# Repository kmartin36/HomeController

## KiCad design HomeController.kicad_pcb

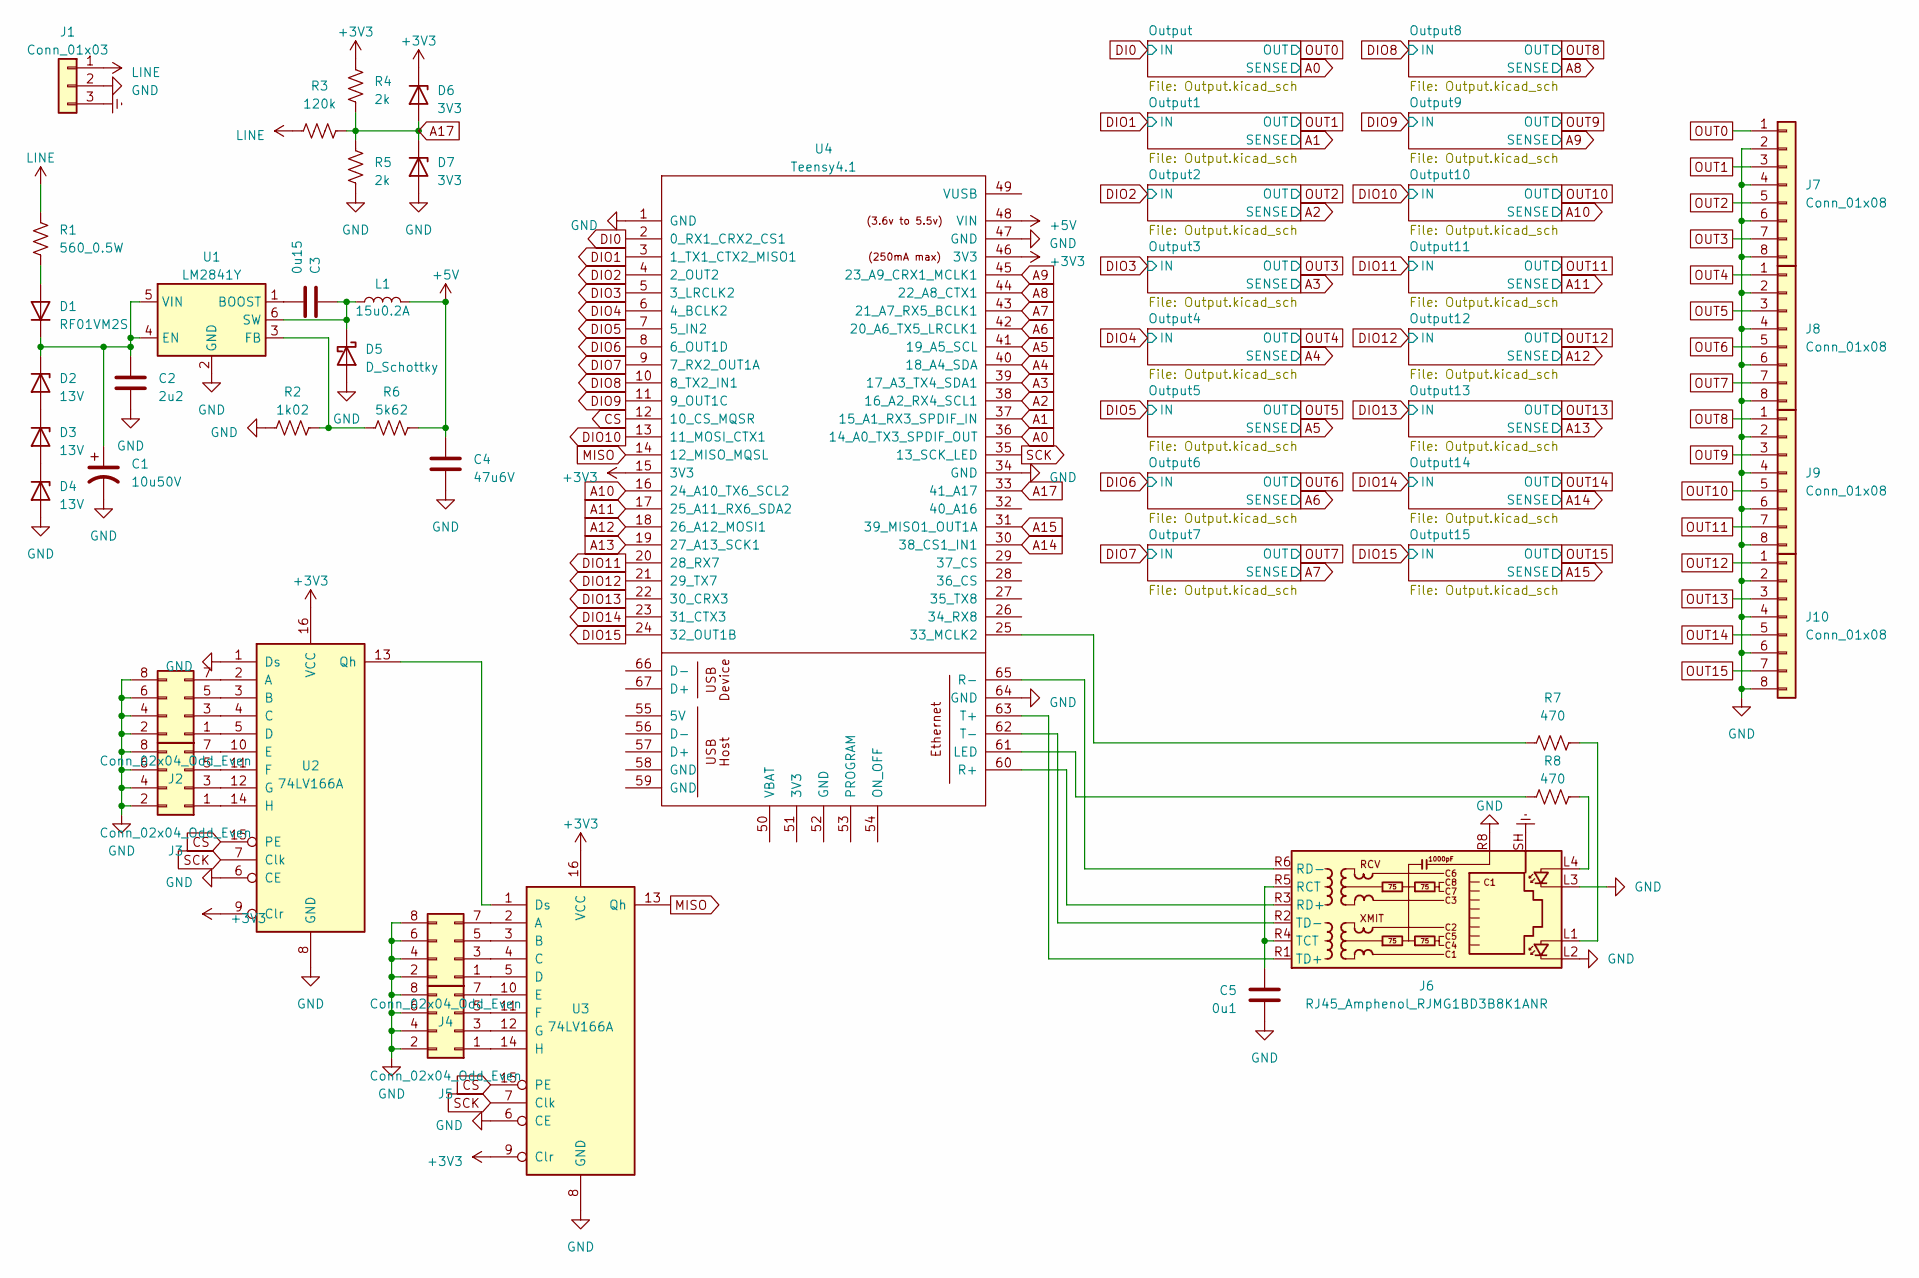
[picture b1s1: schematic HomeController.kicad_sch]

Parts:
C1: 10u50V; L_0805_2012Metric_Pad1.15x1.40mm_HandSolder
C2: 2u2; C_0603_1608Metric_Pad1.08x0.95mm_HandSolder
C3: 0u15; C_0603_1608Metric_Pad1.08x0.95mm_HandSolder
C4: 47u6V; C_0805_2012Metric_Pad1.18x1.45mm_HandSolder
C5: 0u1; C_0603_1608Metric_Pad1.08x0.95mm_HandSolder
D1: RF01VM2S; D_SOD-323
D2, D3, D4: 13V; D_SMA-SMB_Universal_Handsoldering
D5: D_Schottky; D_SC-80_HandSoldering
D6, D7: 3V3; D_SOD-323_HandSoldering
J1: Conn_01x03; PhoenixContact_MCV_1,5_3-G-5.08_1x03_P5.08mm_Vertical
J2, J3, J4, J5: Conn_02x04_Odd_Even; PhoenixContact_MCV_1,5_8-G-5.08_1x08_P5.08mm_Vertical
J6: RJ45_Amphenol_RJMG1BD3B8K1ANR
J7, J8, J9, J10: Conn_01x08; PhoenixContact_MCV_1,5_8-G-5.08_1x08_P5.08mm_Vertical
L1: 15u0.2A; L_0805_2012Metric_Pad1.15x1.40mm_HandSolder
R1: 560_0.5W; R_1210_3225Metric_Pad1.30x2.65mm_HandSolder
R2: 1k02; R_0603_1608Metric_Pad0.98x0.95mm_HandSolder
R3: 120k; R_1206_3216Metric_Pad1.30x1.75mm_HandSolder
R4, R5: 2k; R_0603_1608Metric_Pad0.98x0.95mm_HandSolder
R6: 5k62; R_0603_1608Metric_Pad0.98x0.95mm_HandSolder
R7, R8: 470; R_0603_1608Metric_Pad0.98x0.95mm_HandSolder
U1: LM2841Y; TSOT-23-6
U2, U3: 74LV166A; TSSOP-16_4.4x5mm_P0.65mm
U4: Teensy4.1; Teensy41

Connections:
+3V3: D6.1 (K), R4.1, U2.9 (Clr), U2.16 (VCC), U3.9 (Clr), U3.16 (VCC), U4.15 (3V3), U4.46 (3V3); also elsewhere on the board
+5V: C4.1, L1.2, R6.1, U4.48 (VIN)
A0: U4.36 (14_A0_TX3_SPDIF_OUT); also elsewhere on the board
A1: U4.37 (15_A1_RX3_SPDIF_IN); also elsewhere on the board
A2: U4.38 (16_A2_RX4_SCL1); also elsewhere on the board
A3: U4.39 (17_A3_TX4_SDA1); also elsewhere on the board
A4: U4.40 (18_A4_SDA); also elsewhere on the board
A5: U4.41 (19_A5_SCL); also elsewhere on the board
A6: U4.42 (20_A6_TX5_LRCLK1); also elsewhere on the board
A7: U4.43 (21_A7_RX5_BCLK1); also elsewhere on the board
A8: U4.44 (22_A8_CTX1); also elsewhere on the board
A9: U4.45 (23_A9_CRX1_MCLK1); also elsewhere on the board
A10: U4.16 (24_A10_TX6_SCL2); also elsewhere on the board
A11: U4.17 (25_A11_RX6_SDA2); also elsewhere on the board
A12: U4.18 (26_A12_MOSI1); also elsewhere on the board
A13: U4.19 (27_A13_SCK1); also elsewhere on the board
A14: U4.30 (38_CS1_IN1); also elsewhere on the board
A15: U4.31 (39_MISO1_OUT1A); also elsewhere on the board
A17: D6.2 (A), D7.1 (K), R3.2, R4.2, R5.1, U4.33 (41_A17)
CS: U2.15 (PE), U3.15 (PE), U4.12 (10_CS_MQSR)
DI0: U4.2 (0_RX1_CRX2_CS1); also elsewhere on the board
DIO1: U4.3 (1_TX1_CTX2_MISO1); also elsewhere on the board
DIO2: U4.4 (2_OUT2); also elsewhere on the board
DIO3: U4.5 (3_LRCLK2); also elsewhere on the board
DIO4: U4.6 (4_BCLK2); also elsewhere on the board
DIO5: U4.7 (5_IN2); also elsewhere on the board
DIO6: U4.8 (6_OUT1D); also elsewhere on the board
DIO7: U4.9 (7_RX2_OUT1A); also elsewhere on the board
DIO8: U4.10 (8_TX2_IN1); also elsewhere on the board
DIO9: U4.11 (9_OUT1C); also elsewhere on the board
DIO10: U4.13 (11_MOSI_CTX1); also elsewhere on the board
DIO11: U4.20 (28_RX7); also elsewhere on the board
DIO12: U4.21 (29_TX7); also elsewhere on the board
DIO13: U4.22 (30_CRX3); also elsewhere on the board
DIO14: U4.23 (31_CTX3); also elsewhere on the board
DIO15: U4.24 (32_OUT1B); also elsewhere on the board
Earth: J1.3, J6.SH
GND: C1.2, C2.2, C4.2, C5.2, D4.2 (A), D5.2 (A), D7.2 (A), J1.2, J2.2, J2.4, J2.6, J2.8, J3.2, J3.4, J3.6, J3.8, J4.2, J4.4, J4.6, J4.8, J5.2, J5.4, J5.6, J5.8, J6.L2, J6.L3, J6.R8, J7.2, J7.4, J7.6, J7.8, J8.2, J8.4, J8.6, J8.8, J9.2, J9.4, J9.6, J9.8, J10.2, J10.4, J10.6, J10.8, R2.1, R5.2, U1.2 (GND), U2.1 (Ds), U2.6 (CE), U2.8 (GND), U3.6 (CE), U3.8 (GND), U4.1 (GND), U4.34 (GND), U4.47 (GND), U4.64 (GND); also elsewhere on the board
LINE: J1.1, R1.2, R3.1; also elsewhere on the board
MISO: U3.13 (Qh), U4.14 (12_MISO_MQSL)
unnamed: D1.2 (A), R1.1
unnamed: C1.1, C2.1, D1.1 (K), D2.1 (K), U1.4 (EN), U1.5 (VIN)
unnamed: D2.2 (A), D3.1 (K)
unnamed: D3.2 (A), D4.1 (K)
unnamed: C3.1, D5.1 (K), L1.1, U1.6 (SW)
unnamed: J2.1, U2.5 (D)
unnamed: J2.3, U2.4 (C)
unnamed: J2.5, U2.3 (B)
unnamed: J2.7, U2.2 (A)
unnamed: J3.1, U2.14 (H)
unnamed: J3.3, U2.12 (G)
unnamed: J3.5, U2.11 (F)
unnamed: J3.7, U2.10 (E)
unnamed: J4.1, U3.5 (D)
unnamed: J4.3, U3.4 (C)
unnamed: J4.5, U3.3 (B)
unnamed: J4.7, U3.2 (A)
unnamed: J5.1, U3.14 (H)
unnamed: J5.3, U3.12 (G)
unnamed: J5.5, U3.11 (F)
unnamed: J5.7, U3.10 (E)
unnamed: J6.L1, R7.2
unnamed: J6.L4, R8.2
unnamed: C5.1, J6.R4 (TCT), J6.R5 (RCT)
unnamed: J6.R3 (RD+), U4.60 (R+)
unnamed: J6.R6 (RD-), U4.65 (R-)
unnamed: J6.R1 (TD+), U4.63 (T+)
unnamed: J6.R2 (TD-), U4.62 (T-)
unnamed: C3.2, U1.1 (BOOST)
unnamed: R2.2, R6.2, U1.3 (FB)
unnamed: U2.13 (Qh), U3.1 (Ds)
unnamed: R7.1, U4.25 (33_MCLK2)
unnamed: R8.1, U4.61 (LED)
OUT0: J7.1; also elsewhere on the board
OUT1: J7.3; also elsewhere on the board
OUT2: J7.5; also elsewhere on the board
OUT3: J7.7; also elsewhere on the board
OUT4: J8.1; also elsewhere on the board
OUT5: J8.3; also elsewhere on the board
OUT6: J8.5; also elsewhere on the board
OUT7: J8.7; also elsewhere on the board
OUT8: J9.1; also elsewhere on the board
OUT9: J9.3; also elsewhere on the board
OUT10: J9.5; also elsewhere on the board
OUT11: J9.7; also elsewhere on the board
OUT12: J10.1; also elsewhere on the board
OUT13: J10.3; also elsewhere on the board
OUT14: J10.5; also elsewhere on the board
OUT15: J10.7; also elsewhere on the board
SCK: U2.7 (Clk), U3.7 (Clk), U4.35 (13_SCK_LED)

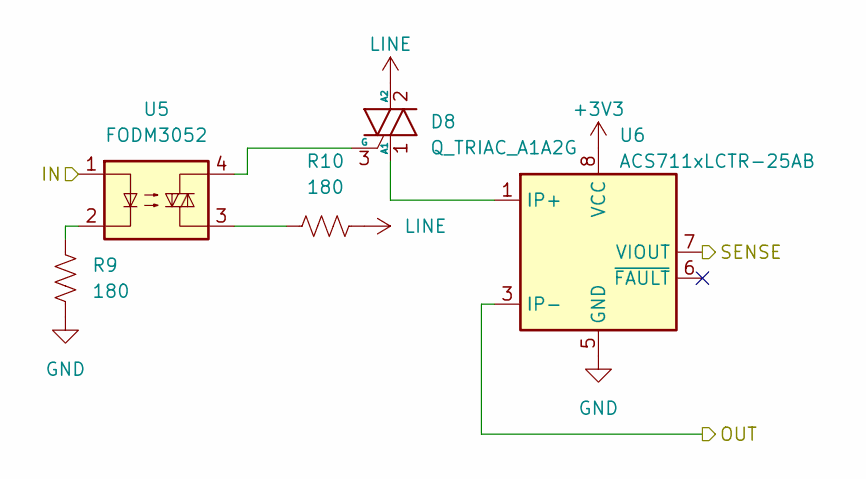
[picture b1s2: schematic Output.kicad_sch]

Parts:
D8: Q_TRIAC_A1A2G; TO-252-2
R9, R10: 180; R_0603_1608Metric_Pad0.98x0.95mm_HandSolder
U5: FODM3052; SMDIP-4_W7.62mm
U6: ACS711xLCTR-25AB; SOIC-8_3.9x4.9mm_P1.27mm

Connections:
+3V3: U6.8 (VCC); also elsewhere on the board
A0: U6.7 (VIOUT); also elsewhere on the board
DI0: U5.1; also elsewhere on the board
GND: R9.2, U6.5 (GND); also elsewhere on the board
LINE: D8.2 (A2), R10.2; also elsewhere on the board
unnamed: D8.1 (A1), U6.1 (IP+), U6.2 (IP+)
unnamed: D8.3 (G), U5.4
unnamed: R9.1, U5.2
unnamed: R10.1, U5.3
OUT0: U6.3 (IP-), U6.4 (IP-); also elsewhere on the board

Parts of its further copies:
D9, D10, D11, D12, D13, D14, D15, D16, D17, D18, D19, D20, D21, D22, D23: Q_TRIAC_A1A2G; TO-252-2
R11, R12, R13, R14, R15, R16, R17, R18, R19, R20, R21, R22, R23, R24, R25, R26, R27, R28, R29, R30, R31, R32, R33, R34, R35, R36, R37, R38, R39, R40: 180; R_0603_1608Metric_Pad0.98x0.95mm_HandSolder
U7, U9, U11, U13, U15, U17, U19, U21, U23, U25, U27, U29, U31, U33, U35: FODM3052; SMDIP-4_W7.62mm
U8, U10, U12, U14, U16, U18, U20, U22, U24, U26, U28, U30, U32, U34, U36: ACS711xLCTR-25AB; SOIC-8_3.9x4.9mm_P1.27mm

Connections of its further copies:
+3V3: U8.8 (VCC), U10.8 (VCC), U12.8 (VCC), U14.8 (VCC), U16.8 (VCC), U18.8 (VCC), U20.8 (VCC), U22.8 (VCC), U24.8 (VCC), U26.8 (VCC), U28.8 (VCC), U30.8 (VCC), U32.8 (VCC), U34.8 (VCC), U36.8 (VCC); also elsewhere on the board
A1: U36.7 (VIOUT); also elsewhere on the board
A2: U10.7 (VIOUT); also elsewhere on the board
A3: U8.7 (VIOUT); also elsewhere on the board
A4: U14.7 (VIOUT); also elsewhere on the board
A5: U12.7 (VIOUT); also elsewhere on the board
A6: U18.7 (VIOUT); also elsewhere on the board
A7: U16.7 (VIOUT); also elsewhere on the board
A8: U22.7 (VIOUT); also elsewhere on the board
A9: U20.7 (VIOUT); also elsewhere on the board
A10: U32.7 (VIOUT); also elsewhere on the board
A11: U24.7 (VIOUT); also elsewhere on the board
A12: U34.7 (VIOUT); also elsewhere on the board
A13: U26.7 (VIOUT); also elsewhere on the board
A14: U28.7 (VIOUT); also elsewhere on the board
A15: U30.7 (VIOUT); also elsewhere on the board
DIO1: U35.1; also elsewhere on the board
DIO2: U9.1; also elsewhere on the board
DIO3: U7.1; also elsewhere on the board
DIO4: U13.1; also elsewhere on the board
DIO5: U11.1; also elsewhere on the board
DIO6: U17.1; also elsewhere on the board
DIO7: U15.1; also elsewhere on the board
DIO8: U21.1; also elsewhere on the board
DIO9: U19.1; also elsewhere on the board
DIO10: U31.1; also elsewhere on the board
DIO11: U23.1; also elsewhere on the board
DIO12: U33.1; also elsewhere on the board
DIO13: U25.1; also elsewhere on the board
DIO14: U27.1; also elsewhere on the board
DIO15: U29.1; also elsewhere on the board
GND: R11.2, R13.2, R15.2, R17.2, R19.2, R21.2, R23.2, R25.2, R27.2, R29.2, R31.2, R33.2, R35.2, R37.2, R39.2, U8.5 (GND), U10.5 (GND), U12.5 (GND), U14.5 (GND), U16.5 (GND), U18.5 (GND), U20.5 (GND), U22.5 (GND), U24.5 (GND), U26.5 (GND), U28.5 (GND), U30.5 (GND), U32.5 (GND), U34.5 (GND), U36.5 (GND); also elsewhere on the board
LINE: D9.2 (A2), D10.2 (A2), D11.2 (A2), D12.2 (A2), D13.2 (A2), D14.2 (A2), D15.2 (A2), D16.2 (A2), D17.2 (A2), D18.2 (A2), D19.2 (A2), D20.2 (A2), D21.2 (A2), D22.2 (A2), D23.2 (A2), R12.2, R14.2, R16.2, R18.2, R20.2, R22.2, R24.2, R26.2, R28.2, R30.2, R32.2, R34.2, R36.2, R38.2, R40.2; also elsewhere on the board
unnamed: D9.1 (A1), U8.1 (IP+), U8.2 (IP+)
unnamed: D9.3 (G), U7.4
unnamed: D10.1 (A1), U10.1 (IP+), U10.2 (IP+)
unnamed: D10.3 (G), U9.4
unnamed: D11.1 (A1), U12.1 (IP+), U12.2 (IP+)
unnamed: D11.3 (G), U11.4
unnamed: D12.1 (A1), U14.1 (IP+), U14.2 (IP+)
unnamed: D12.3 (G), U13.4
unnamed: D13.1 (A1), U16.1 (IP+), U16.2 (IP+)
unnamed: D13.3 (G), U15.4
unnamed: D14.1 (A1), U18.1 (IP+), U18.2 (IP+)
unnamed: D14.3 (G), U17.4
unnamed: D15.1 (A1), U20.1 (IP+), U20.2 (IP+)
unnamed: D15.3 (G), U19.4
unnamed: D16.1 (A1), U22.1 (IP+), U22.2 (IP+)
unnamed: D16.3 (G), U21.4
unnamed: D17.1 (A1), U24.1 (IP+), U24.2 (IP+)
unnamed: D17.3 (G), U23.4
unnamed: D18.1 (A1), U26.1 (IP+), U26.2 (IP+)
unnamed: D18.3 (G), U25.4
unnamed: D19.1 (A1), U28.1 (IP+), U28.2 (IP+)
unnamed: D19.3 (G), U27.4
unnamed: D20.1 (A1), U30.1 (IP+), U30.2 (IP+)
unnamed: D20.3 (G), U29.4
unnamed: D21.1 (A1), U32.1 (IP+), U32.2 (IP+)
unnamed: D21.3 (G), U31.4
unnamed: D22.1 (A1), U34.1 (IP+), U34.2 (IP+)
unnamed: D22.3 (G), U33.4
unnamed: D23.1 (A1), U36.1 (IP+), U36.2 (IP+)
unnamed: D23.3 (G), U35.4
unnamed: R11.1, U7.2
unnamed: R12.1, U7.3
unnamed: R13.1, U9.2
unnamed: R14.1, U9.3
unnamed: R15.1, U11.2
unnamed: R16.1, U11.3
unnamed: R17.1, U13.2
unnamed: R18.1, U13.3
unnamed: R19.1, U15.2
unnamed: R20.1, U15.3
unnamed: R21.1, U17.2
unnamed: R22.1, U17.3
unnamed: R23.1, U19.2
unnamed: R24.1, U19.3
unnamed: R25.1, U21.2
unnamed: R26.1, U21.3
unnamed: R27.1, U23.2
unnamed: R28.1, U23.3
unnamed: R29.1, U25.2
unnamed: R30.1, U25.3
unnamed: R31.1, U27.2
unnamed: R32.1, U27.3
unnamed: R33.1, U29.2
unnamed: R34.1, U29.3
unnamed: R35.1, U31.2
unnamed: R36.1, U31.3
unnamed: R37.1, U33.2
unnamed: R38.1, U33.3
unnamed: R39.1, U35.2
unnamed: R40.1, U35.3
OUT1: U36.3 (IP-), U36.4 (IP-); also elsewhere on the board
OUT2: U10.3 (IP-), U10.4 (IP-); also elsewhere on the board
OUT3: U8.3 (IP-), U8.4 (IP-); also elsewhere on the board
OUT4: U14.3 (IP-), U14.4 (IP-); also elsewhere on the board
OUT5: U12.3 (IP-), U12.4 (IP-); also elsewhere on the board
OUT6: U18.3 (IP-), U18.4 (IP-); also elsewhere on the board
OUT7: U16.3 (IP-), U16.4 (IP-); also elsewhere on the board
OUT8: U22.3 (IP-), U22.4 (IP-); also elsewhere on the board
OUT9: U20.3 (IP-), U20.4 (IP-); also elsewhere on the board
OUT10: U32.3 (IP-), U32.4 (IP-); also elsewhere on the board
OUT11: U24.3 (IP-), U24.4 (IP-); also elsewhere on the board
OUT12: U34.3 (IP-), U34.4 (IP-); also elsewhere on the board
OUT13: U26.3 (IP-), U26.4 (IP-); also elsewhere on the board
OUT14: U28.3 (IP-), U28.4 (IP-); also elsewhere on the board
OUT15: U30.3 (IP-), U30.4 (IP-); also elsewhere on the board

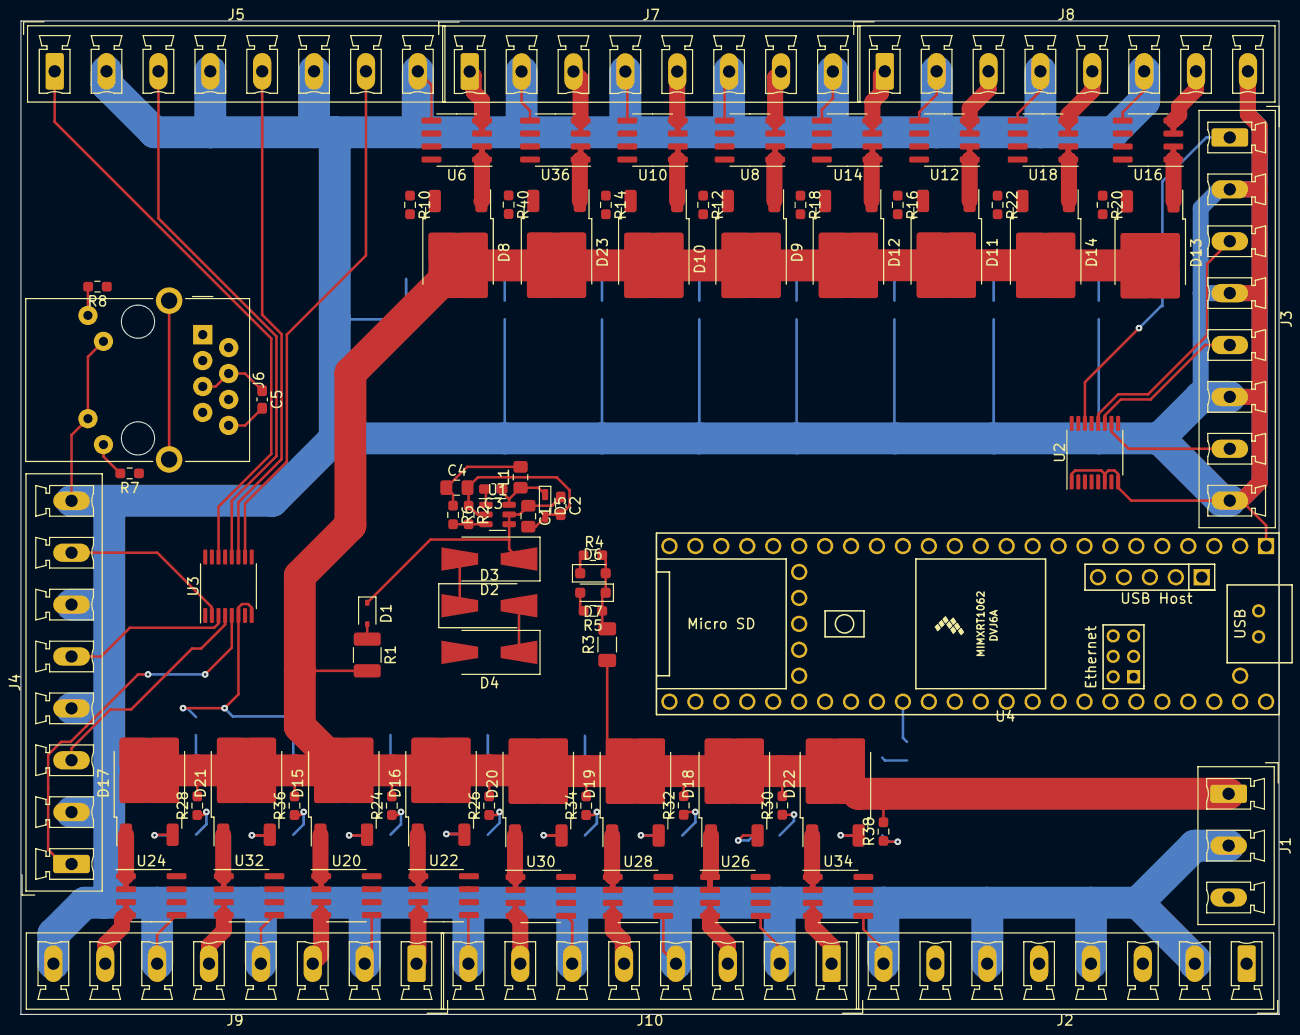
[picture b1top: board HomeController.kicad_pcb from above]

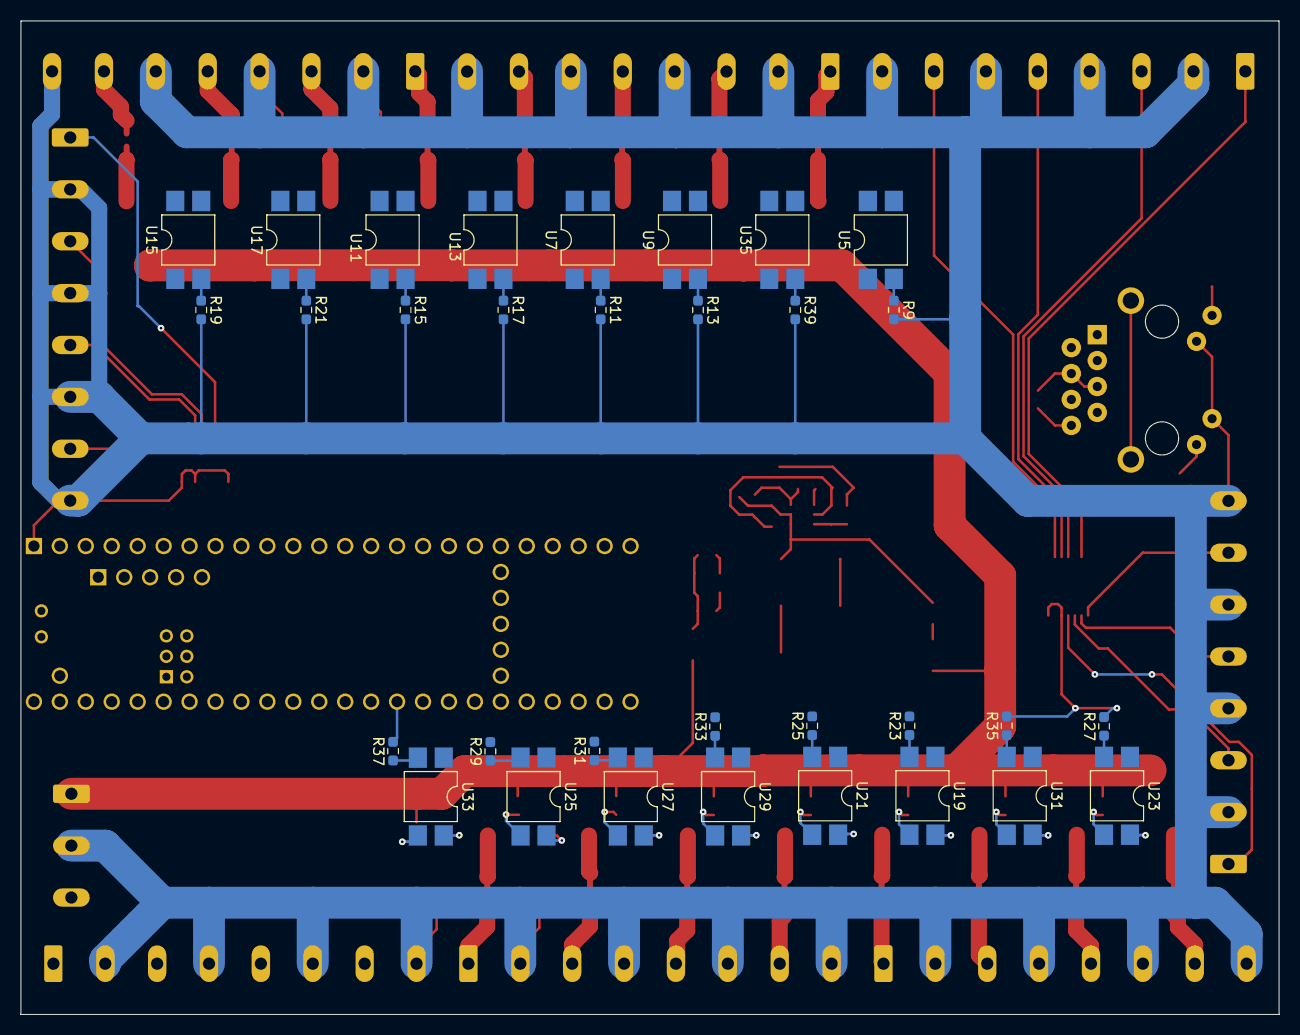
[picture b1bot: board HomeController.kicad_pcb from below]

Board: 2 copper layers, 123.2 x 97.3 mm, 115 parts (32 on the bottom side), 154 nets.

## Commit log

2024-06-11 Adding submodules for the teensy symbol and footprint library repositories
2024-06-12 Adding outputs Setting teensy pins Changed shift register chip Set main ground to neutral line and deriving power from line voltage
2024-06-13 Assing the rest of the packages
2024-06-13 Starting rough placement
2024-07-02 Placement 1st draft done Routing started Changed some footprints and swapped some pins to make routing easier Added grounds for each output
2024-07-04 More routing
